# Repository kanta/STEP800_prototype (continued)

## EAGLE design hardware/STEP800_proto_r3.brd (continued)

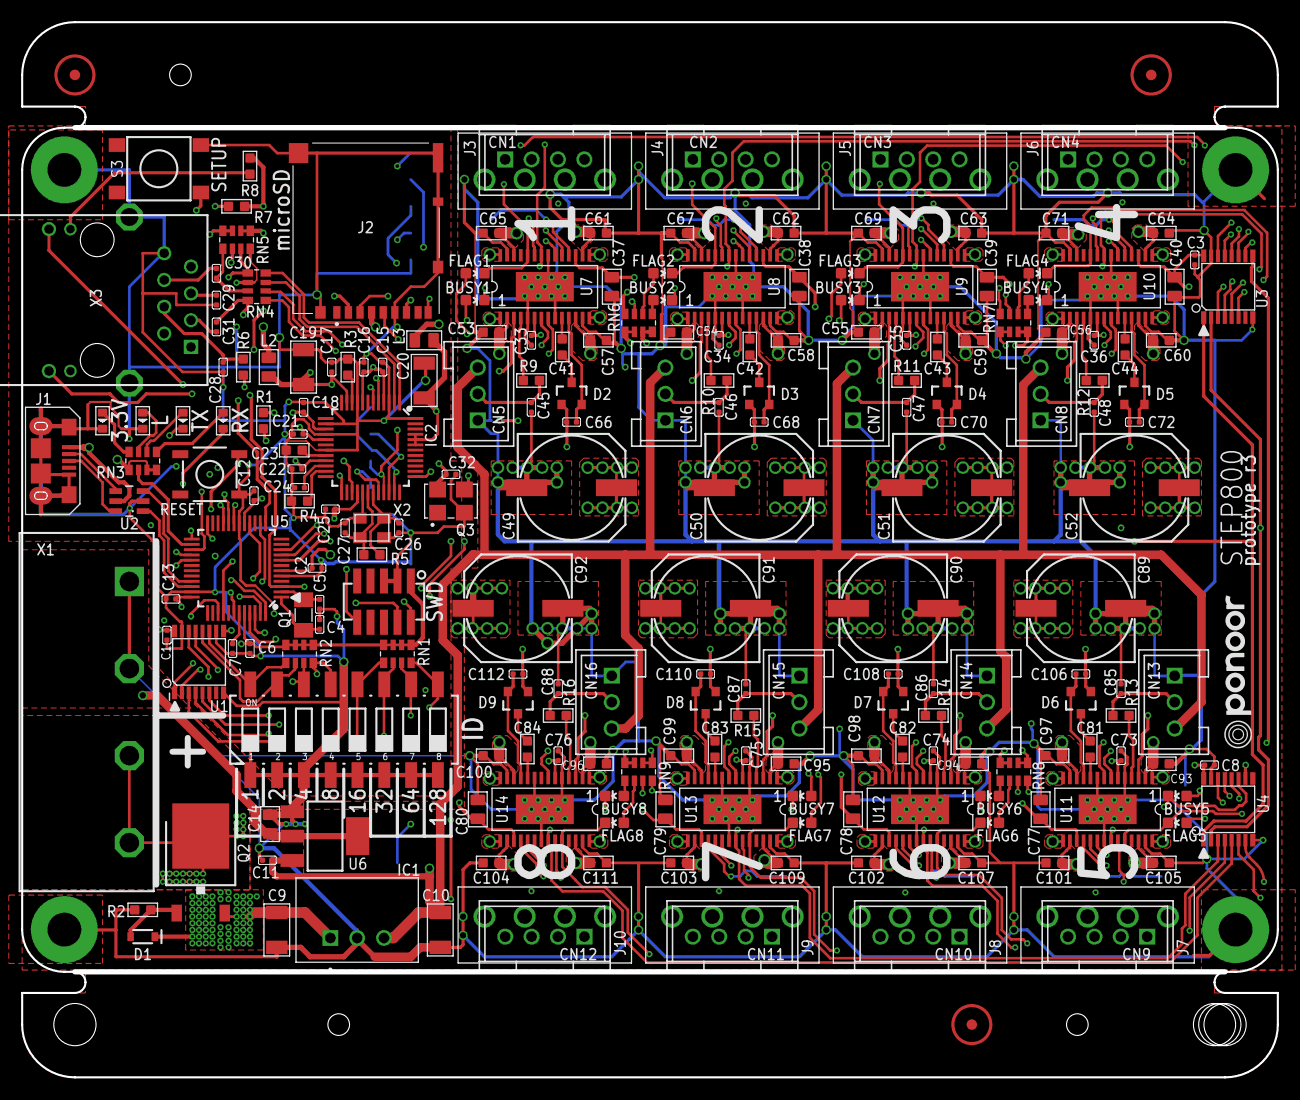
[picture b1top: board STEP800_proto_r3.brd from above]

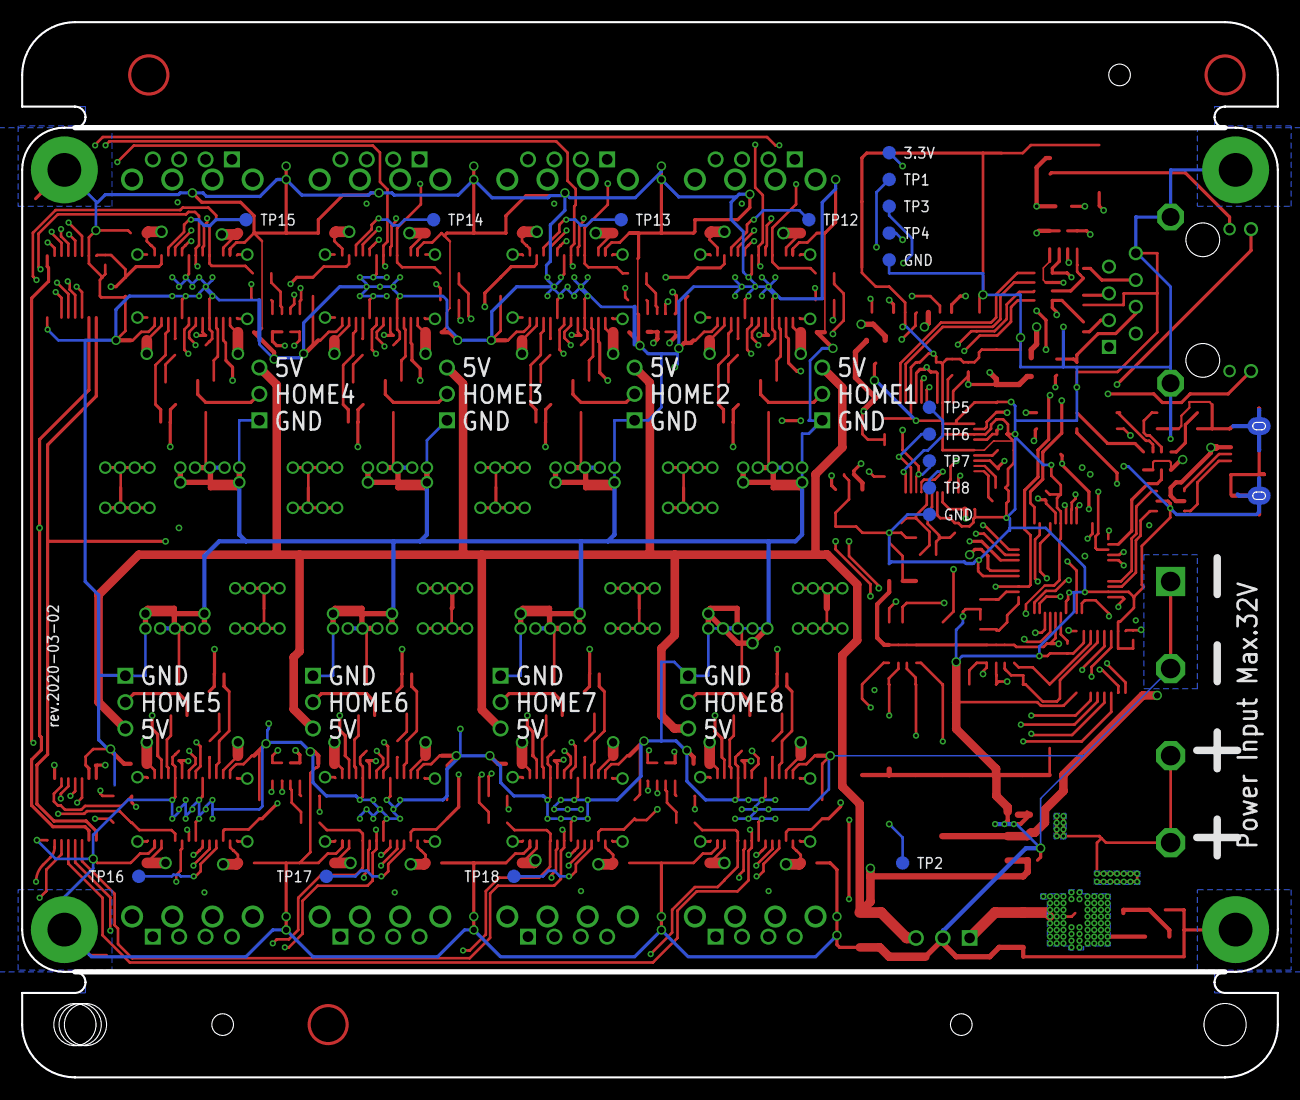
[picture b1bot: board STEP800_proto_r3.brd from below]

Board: 4 copper layers, 119.0 x 100.0 mm, 246 parts (18 on the bottom side), 200 nets.

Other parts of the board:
U$2: PONOOR_TEXT_15MM

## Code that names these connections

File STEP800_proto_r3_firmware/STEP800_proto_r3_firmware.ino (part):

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byte shiftResistorValue[3];

// L6470
#define L6470_MISO	6	// D6 /SERCOM3/PAD[2] miso
#define L6470_MOSI	11	// D11/SERCOM3/PAD[0] mosi
#define L6470_SCK	12	// D12/SERCOM3/PAD[3] sck
//SPIClass altSPI (&sercom1, 12, 13, 11, SPI_PAD_0_SCK_1, SERCOM_RX_PAD_3);
SPIClass L6470SPI(&sercom3, L6470_MISO, L6470_SCK, L6470_MOSI, SPI_PAD_0_SCK_3, SERCOM_RX_PAD_2);// MISO/SCK/MOSI pins

#define L6470_CS_PIN A0
#define L6470_RESET_PIN A2

AutoDriver stepper[] = {
	AutoDriver(7, L6470_CS_PIN, L6470_RESET_PIN),
	AutoDriver(6, L6470_CS_PIN, L6470_RESET_PIN),
	AutoDriver(5, L6470_CS_PIN, L6470_RESET_PIN),
	AutoDriver(4, L6470_CS_PIN, L6470_RESET_PIN),
	AutoDriver(3, L6470_CS_PIN, L6470_RESET_PIN),
	AutoDriver(2, L6470_CS_PIN, L6470_RESET_PIN),
	AutoDriver(1, L6470_CS_PIN, L6470_RESET_PIN),
	AutoDriver(0, L6470_CS_PIN, L6470_RESET_PIN)
};

// microSD slot
#define SD_CS_PIN	4u
#define SD_DETECT_PIN	A4

#define SETUP_SW_PIN	5u

// servo mode
uint32_t lastServoUpdateTime;
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{
	//setUSBPriority();
	pinMode(ledPin, OUTPUT);
	pinMode(SD_CS_PIN, OUTPUT);
	pinMode(LATCH3, OUTPUT);
	pinMode(SD_DETECT_PIN, INPUT_PULLUP);
	pinMode(SETUP_SW_PIN, INPUT_PULLUP);

	SerialUSB.begin(115200);

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
	// Prepare pins
	pinMode(L6470_RESET_PIN, OUTPUT);
	pinMode(L6470_CS_PIN, OUTPUT);
	pinMode(L6470_MOSI, OUTPUT);
	pinMode(L6470_MISO, INPUT);
	pinMode(L6470_SCK, OUTPUT);

	// Shift registers
	SPI3.begin();
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	digitalWrite(L6470_RESET_PIN, LOW);
	delay(10);
	digitalWrite(L6470_RESET_PIN, HIGH);
	digitalWrite(L6470_CS_PIN, HIGH);

	// Start SPI for L6470
	L6470SPI.begin();
	pinPeripheral(L6470_MOSI, PIO_SERCOM_ALT);
	pinPeripheral(L6470_SCK, PIO_SERCOM_ALT);
	pinPeripheral(L6470_MISO, PIO_SERCOM_ALT);
	L6470SPI.setDataMode(SPI_MODE3);
	delay(10);

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
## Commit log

2020-06-15 added .gitignore
2020-06-15 source code initial commit
2020-06-19 added some STATUS debug code.
2020-07-02 Overall update for the sketch and the library
2020-07-10 update servo mode and AutoDriver library
2020-07-10 Variables initialization and constants name updated. Added hardware design files.
2020-07-13 Update .gitignore
    added .vs directory
2020-07-13 Changed some variables name and initialization, as same as STEP400proto_r4
2021-02-14 Added OSC float->int cast helper
2021-02-18 Fixed getInt bug
2021-02-18 Added platformio prj. Implemented servo call
2021-02-18 Changed OSC msg setKVAL to setKval
2021-02-20 fixed /getSpeedProfile 255 bug
